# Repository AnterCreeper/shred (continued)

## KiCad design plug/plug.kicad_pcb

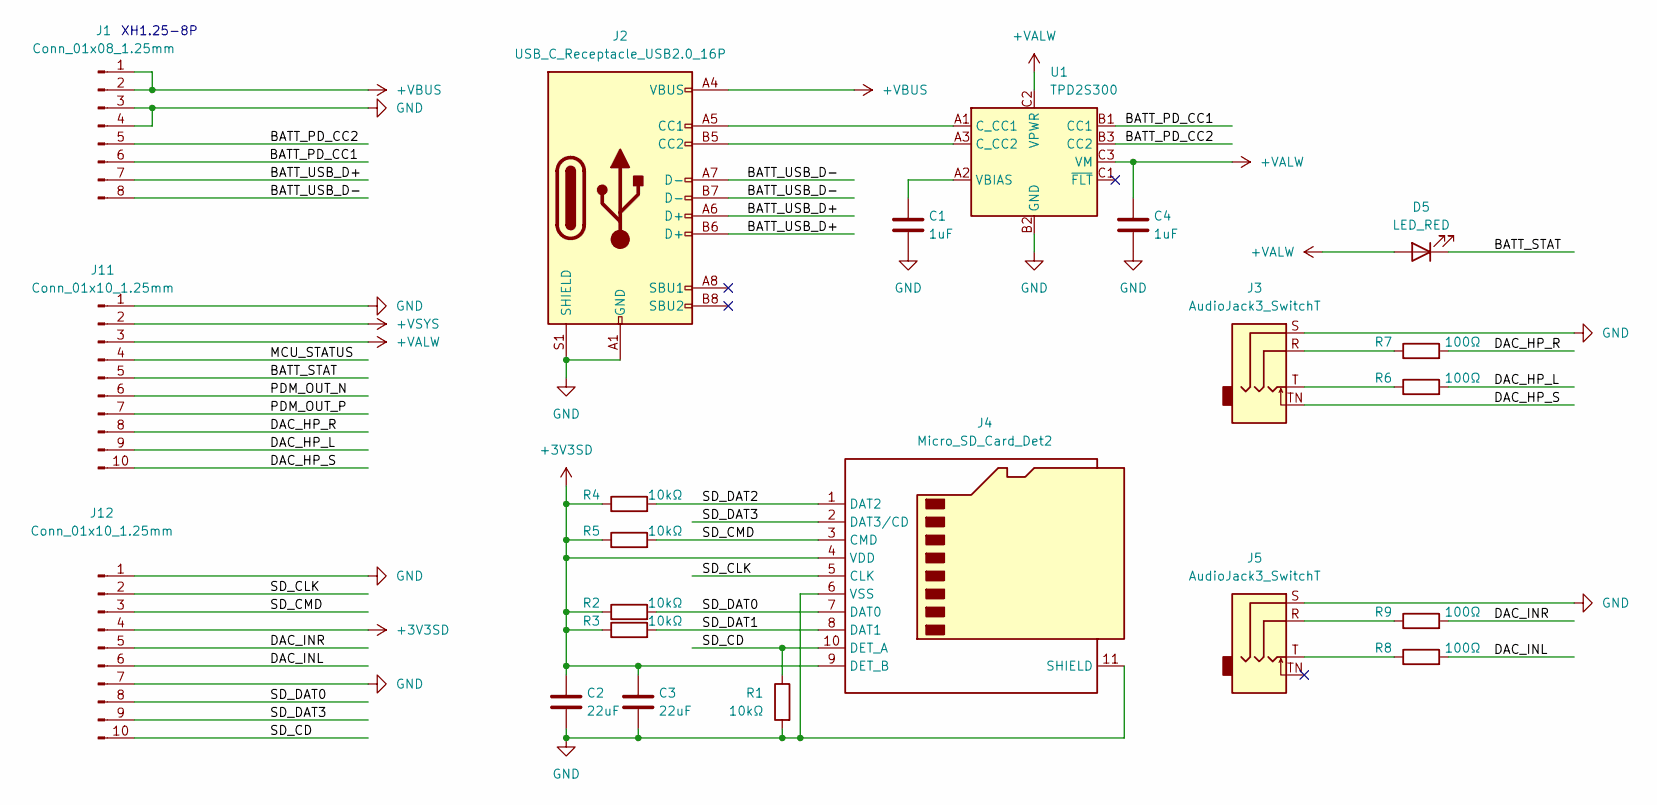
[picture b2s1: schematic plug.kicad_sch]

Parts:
C1, C4: 1uF; C_0402_1005Metric
C2, C3: 22uF; C_0603_1608Metric
D5: LED_RED; D_0603_1608Metric
J1: Conn_01x08_1.25mm; Molex_PicoBlade_53047-0810_1x08_P1.25mm_Vertical
J2: USB_C_Receptacle_USB2.0_16P; USB_C_Receptacle_XKB_U262-16XN-4BVC11
J3, J5: AudioJack3_SwitchT; Jack_3.5mm_KoreanHropartsElec_PJ-327D-5A_Horizontal
J4: Micro_SD_Card_Det2; microSD_HC_Molex_104031-0811
J11, J12: Conn_01x10_1.25mm; Molex_PicoBlade_53047-1010_1x10_P1.25mm_Vertical
R1, R2, R3, R4, R5: 10kΩ; R_0402_1005Metric
R6, R7, R8, R9: 100Ω; R_0402_1005Metric
U1: TPD2S300; Texas_DSBGA-9_1.36x1.36mm_Layout3x3_P0.4mm

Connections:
+3V3SD: C2.1, C3.1, J4.4 (VDD), J4.9 (DET_B), J12.4, R2.1, R3.1, R4.1, R5.1
+VALW: C4.1, D5.2 (A), J11.3, U1.C2 (VPWR), U1.C3 (VM)
+VBUS: J1.1, J1.2, J2.A4 (VBUS), J2.A9 (VBUS), J2.B4 (VBUS), J2.B9 (VBUS)
+VSYS: J11.2
/BATT_PD_CC1: J1.6, U1.B1 (CC1)
/BATT_PD_CC2: J1.5, U1.B3 (CC2)
/BATT_STAT: D5.1 (K), J11.5
/BATT_USB_D+: J1.7, J2.A6 (D+), J2.B6 (D+)
/BATT_USB_D-: J1.8, J2.A7 (D-), J2.B7 (D-)
/DAC_HP_L: J11.9, R6.2
/DAC_HP_R: J11.8, R7.2
/DAC_HP_S: J3.TN, J11.10
/DAC_INL: J12.6, R8.2
/DAC_INR: J12.5, R9.2
/MCU_STATUS: J11.4
/PDM_OUT_N: J11.6
/PDM_OUT_P: J11.7
/SD_CD: J4.10 (DET_A), J12.10, R1.1
/SD_CLK: J4.5 (CLK), J12.2
/SD_CMD: J4.3 (CMD), J12.3, R5.2
/SD_DAT0: J4.7 (DAT0), J12.8, R2.2
/SD_DAT1: J4.8 (DAT1), R3.2
/SD_DAT2: J4.1 (DAT2), R4.2
/SD_DAT3: J4.2 (DAT3/CD), J12.9
GND: C1.2, C2.2, C3.2, C4.2, J1.3, J1.4, J2.A1 (GND), J2.A12 (GND), J2.B1 (GND), J2.B12 (GND), J2.S1 (SHIELD), J3.S, J4.6 (VSS), J4.11 (SHIELD), J5.S, J11.1, J12.1, J12.7, R1.2, U1.B2 (GND); also elsewhere on the board
unnamed: J2.A5 (CC1), U1.A1 (C_CC1)
unnamed: J2.B5 (CC2), U1.A3 (C_CC2)
unnamed: J3.R, R7.1
unnamed: J3.T, R6.1
unnamed: J5.R, R9.1
unnamed: J5.T, R8.1
unnamed: C1.1, U1.A2 (VBIAS)

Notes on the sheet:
XH1.25-8P

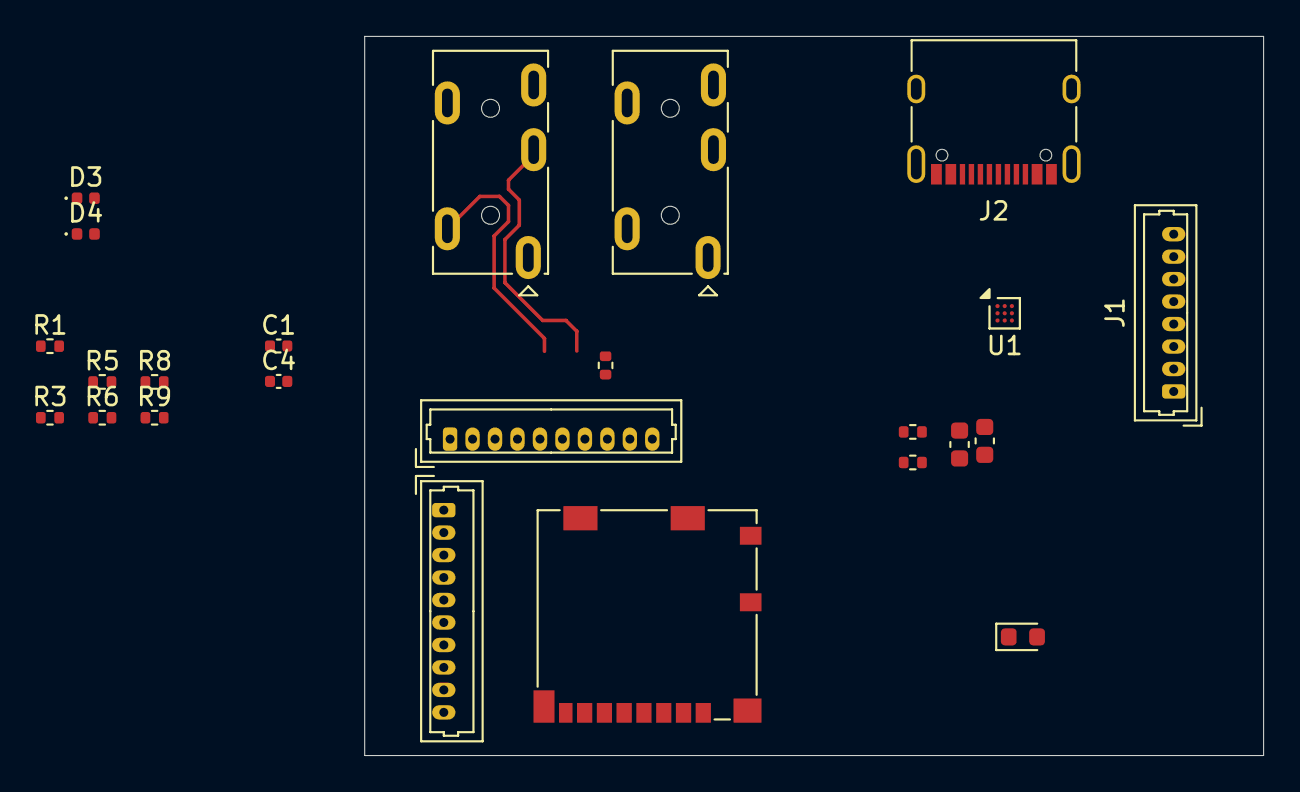
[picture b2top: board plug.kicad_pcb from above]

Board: 2 copper layers, 50.0 x 40.0 mm, 24 parts (0 on the bottom side), 28 nets.

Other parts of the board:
D3, D4: D_TVS; D_0402_1005Metric

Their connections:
GND: D3.1 (A1), D4.1 (A1); also elsewhere on the board

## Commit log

2026-03-26 first commit.
2026-03-30 update.
2026-03-31 upload logo.
